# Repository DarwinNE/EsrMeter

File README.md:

# EsrMeter
An open hardware in-circuit ESR meter for electrolytic capacitors.

This circuit is based on a PIC16F883 that controls a simple lock-in circuit to measure in circuit the ESR and in some cases the capacitance of electrolytic capacitors.

The circuit has been designed by Davide Bucci, the PCB by Etenmenanki using Eagle. The size of the PCBs is compatible with the free version of the program.

A description (in italian language) of the circuit can be found here: https://www.electroyou.it/darwinne/wiki/misurare-esr-di-condensatori-con-circuito-lock-in

Two versions of the PCB exist. The first one has the digital and analog parts split in two. This approach has the advantage that one can test the analog board with something different from the PIC16F883 (i.e. a STM32 or an Arduino board, for instance). The version with the two boards separated requires some corrections, look at the associated files if you try to build them.
The second version has all digital and analog circuits on the same board and it is much more compact. I ordered the PCB on July 24, 2022, I received them and assembled a first prototype at the end of August 2022. It worked at the first attempt, but there is a shift in low ESR values and moderate to large capacitance (>300µF) that I am currently (mid Sept 2022) investigating.

All components are SMD. In the "all in one" boards, two different versions of the PIC16F883 can be used to cope with the pandemic scarcity of components: SOIC and SSOP. I think the PIC16F886 can be used at the place of the PIC16F883 with minimal changes.

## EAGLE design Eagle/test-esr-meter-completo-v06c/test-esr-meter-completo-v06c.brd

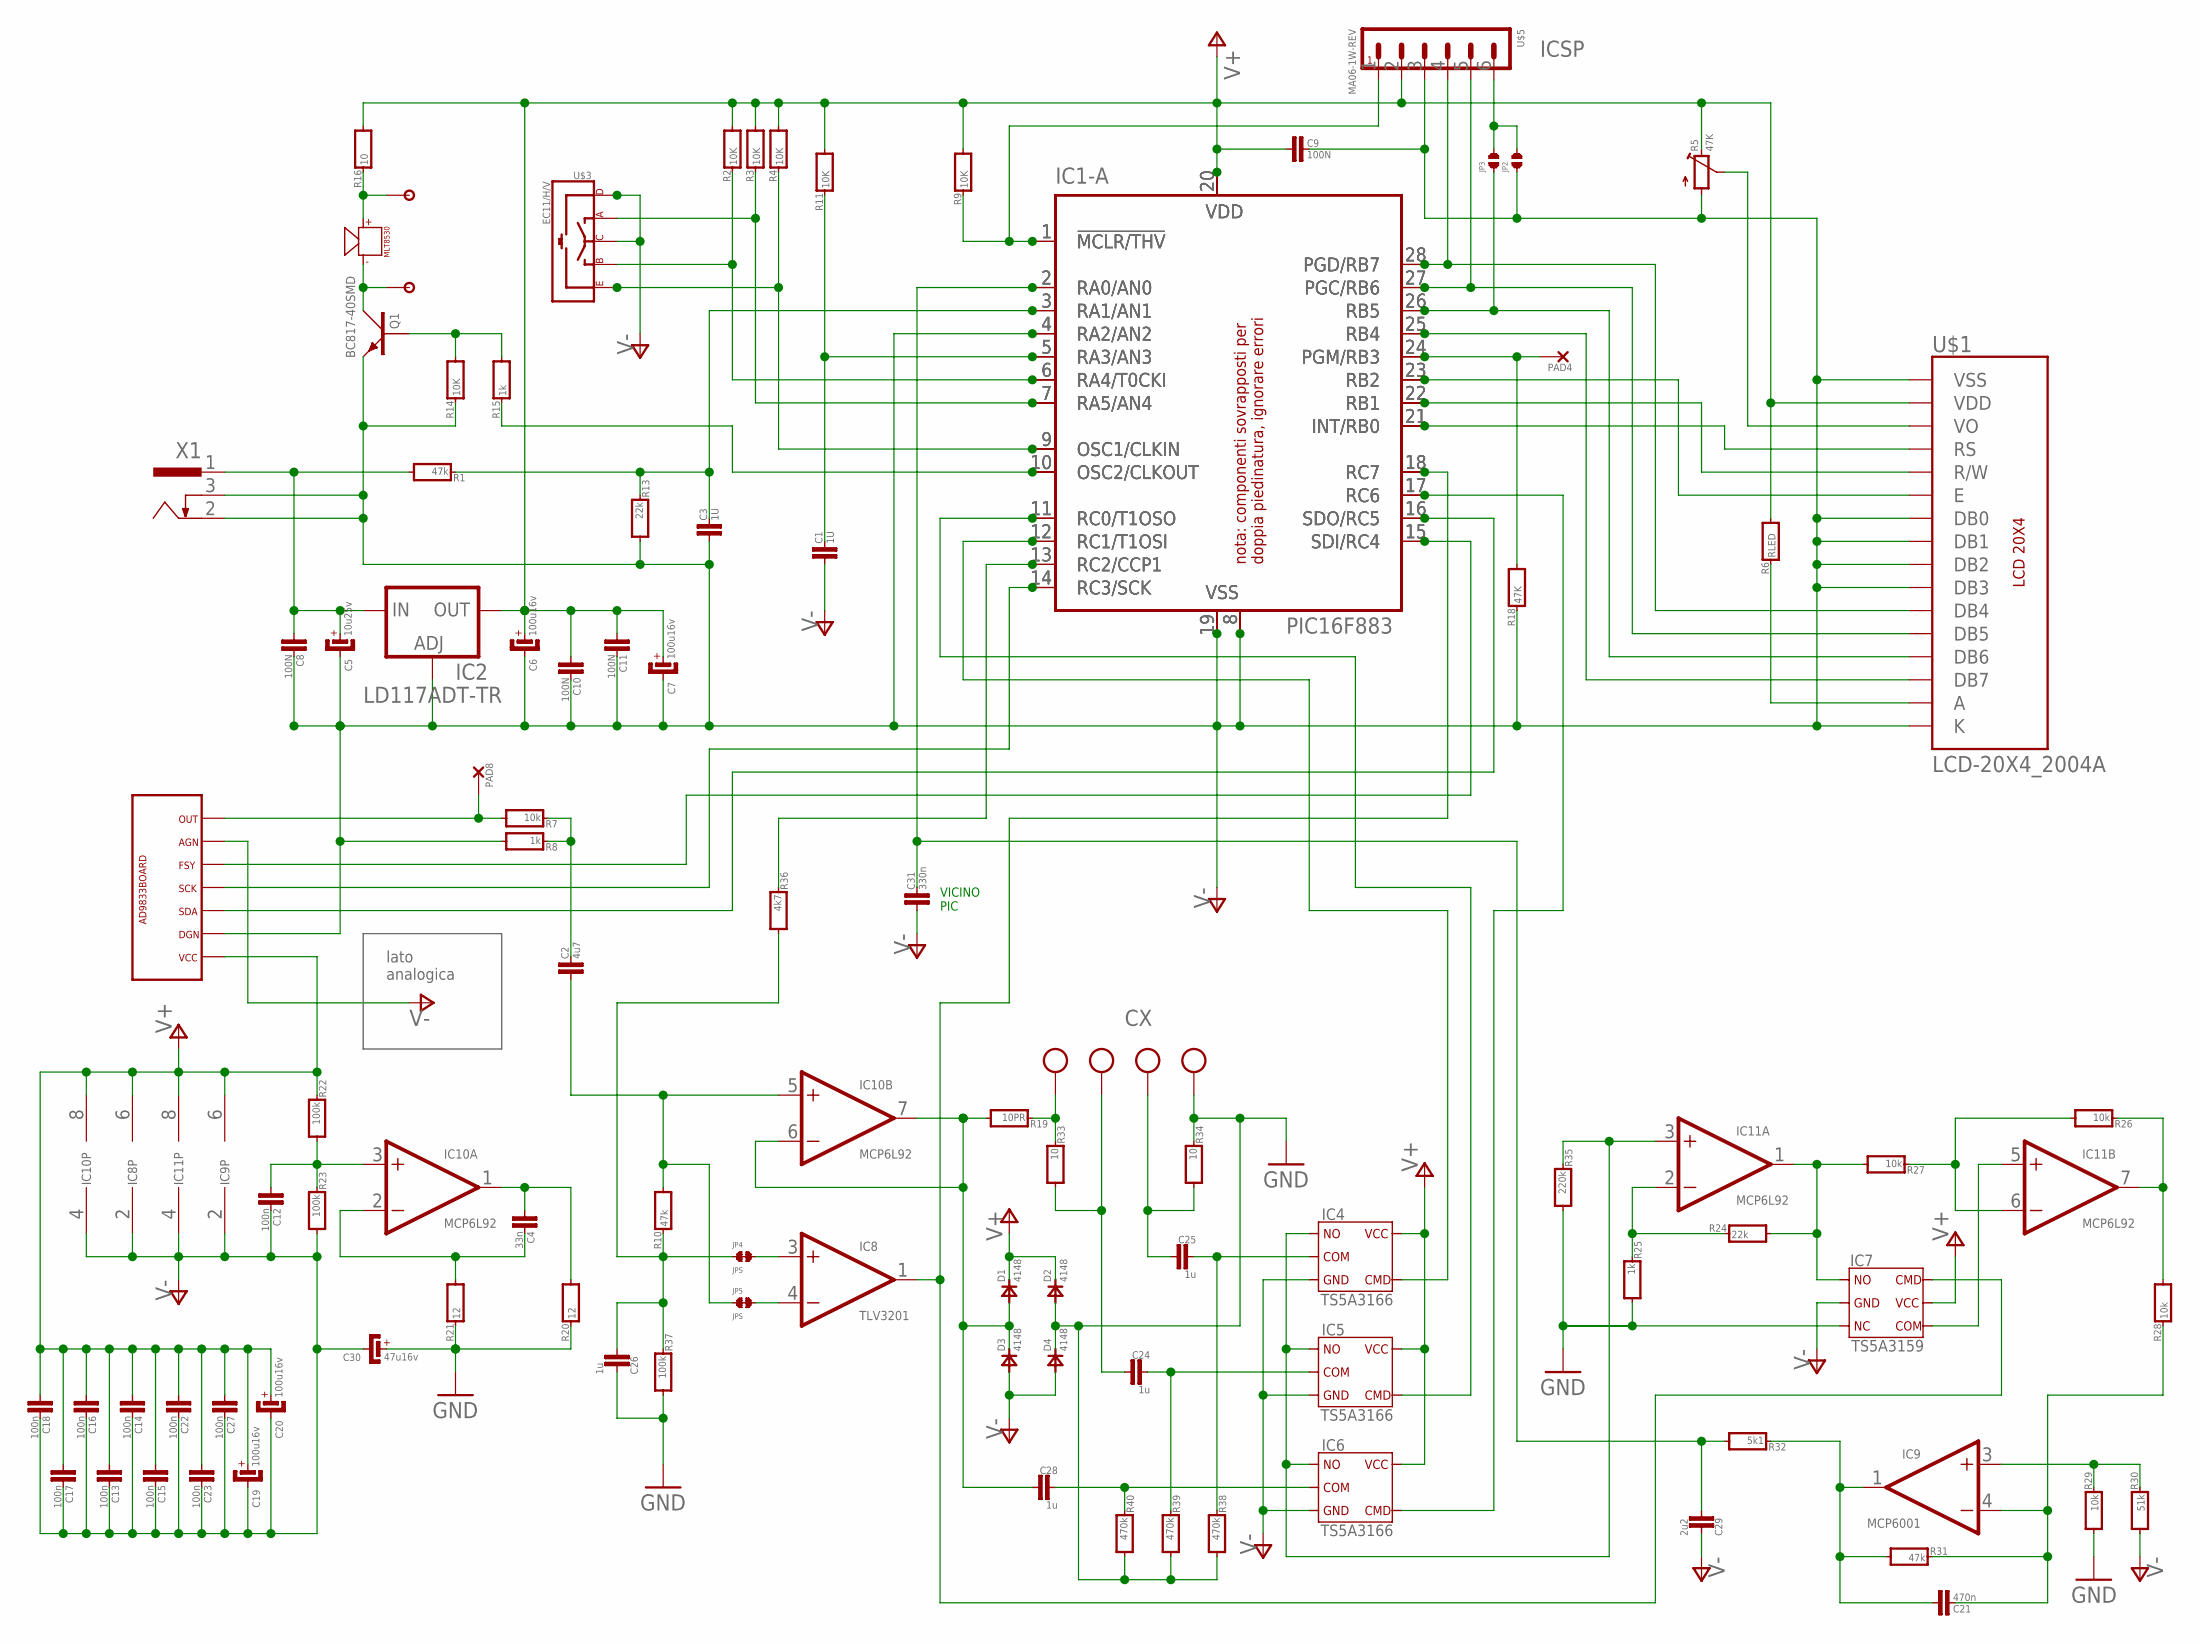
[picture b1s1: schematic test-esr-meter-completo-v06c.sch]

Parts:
C1, C3: 1U; C0805K
C2: 4u7; C0805K
C4: 33n; C0805K
C5: 10u25v; SMC_D
C6, C7, C19, C20: 100u16v; SMC_D
C8, C9, C10, C11: 100N; C0805K
C12, C13, C14, C15, C16, C17, C18, C22, C23, C27: 100n; C0805K
C21: 470n; C0805K
C24, C25, C26, C28: 1u; C0805K
C29: 2u2; C0805K
C30: 47u16v; SMC_B
C31: 330n; C0805K
D1, D2, D3, D4: 4148; SOD80C
IC1-A: PIC16F883; SO28W
IC2: LD117ADT-TR; DPACK
IC3: PIC16F872SS; SSOP28
IC4, IC5, IC6: TS5A3166; SOT23-5
IC7: TS5A3159; SOT23-6
IC8: TLV3201; SOT23-5
IC9: MCP6001; SOT23-5
IC10, IC11: MCP6L92; SO08
JP2, JP3: JPO
JP4, JP5: JPS
PAD4, PAD8: SMD2; SMD1,27-2,54
Q1: BC817-40SMD; SOT23-BEC
R1, R10, R31: 47k; R0805
R2, R3, R4, R9, R11, R14: 10K; R0805
R5: 47K; RTRIM3339P
R6: RLED; R0805
R7, R26, R27, R28, R29: 10k; R0805
R8, R15, R25: 1k; R0805
R13, R24: 22k; R0805
R16, R33, R34: 10; R0805
R18: 47K; R0805
R19: 10PR; R0805
R20, R21: 12; R0805
R22, R23, R37: 100k; R0805
R30: 51k; R0805
R32: 5k1; R0805
R35: 220k; R0805
R36: 4k7; R0805
R38, R39, R40: 470k; R0805
U$1: LCD-20X4_2004A
U$2: MLT-8530
U$3: EC11/H/V; EC11/V/H
U$4: AD9833BOARD
U$5: MA06-1W-REV
U$6, U$7: PIAZ08
X1: SCD-014A; SCD-014-A
X2: MKDSN1,5/4-5,08

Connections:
GND: C26.2, C30.+, D2.A, D4.C, IC7.3 (NC), R20.1, R21.1, R25.2, R29.2, R34.1, R35.2, R37.2, R38.2, R39.2, R40.2, X2.4
unnamed: IC1-A.10 (OSC2/CLKOUT), IC3.10 (OSC2/CLKOUT), R15.1
unnamed: C26.1, JP4.P$1, R10.1, R36.2, R37.1
unnamed: Q1.B, R14.2, R15.2
unnamed: IC1-A.28 (PGD/RB7), IC3.28 (PGD/RB7), U$1.11 (DB4), U$5.4
unnamed: IC1-A.14 (RC3/SCK), IC3.14 (RC3/SCK), U$4.SCK
unnamed: IC1-A.16 (SDO/RC5), IC3.16 (SDO/RC5), U$4.SDA
unnamed: IC1-A.15 (SDI/RC4), IC3.15 (SDI/RC4), U$4.FSY
unnamed: IC1-A.27 (PGC/RB6), IC3.27 (PGC/RB6), U$1.12 (DB5), U$5.5
unnamed: R5.2 (S), U$1.3 (VO)
unnamed: C2.2, IC10.5 (+IN), JP5.P$1, R10.2
unnamed: IC1-A.25 (RB4), IC3.25 (RB4), U$1.14 (DB7)
unnamed: C29.1, C31.1, IC1-A.2 (RA0/AN0), IC3.2 (RA0/AN0), R32.2
unnamed: C3.1, IC1-A.3 (RA1/AN1), IC3.3 (RA1/AN1), R1.1, R13.1
unnamed: C1.1, IC1-A.5 (RA3/AN3), IC3.5 (RA3/AN3), R11.1
unnamed: IC1-A.23 (RB2), IC3.23 (RB2), U$1.6 (E)
unnamed: IC1-A.22 (RB1), IC3.22 (RB1), U$1.5 (R/W)
unnamed: IC1-A.21 (INT/RB0), IC3.21 (INT/RB0), U$1.4 (RS)
unnamed: IC1-A.6 (RA4/T0CKI), IC3.6 (RA4/T0CKI), R2.1, U$3.B
unnamed: IC1-A.7 (RA5/AN4), IC3.7 (RA5/AN4), R3.1, U$3.A
unnamed: IC1-A.9 (OSC1/CLKIN), IC3.9 (OSC1/CLKIN), R4.1, U$3.E, U$3.E2
unnamed: IC1-A.17 (RC6), IC3.17 (RC6), IC6.4 (CMD)
unnamed: IC1-A.12 (RC1/T1OSI), IC3.12 (RC1/T1OSI), IC4.4 (CMD)
unnamed: IC1-A.11 (RC0/T1OSO), IC3.11 (RC0/T1OSO), IC5.4 (CMD)
unnamed: C24.1, R33.2, X2.2
unnamed: R6.1, U$1.15 (A)
unnamed: IC1-A.24 (PGM/RB3), IC3.24 (PGM/RB3), PAD4.1, R18.2
unnamed: IC1-A.18 (RC7), IC3.18 (RC7), IC7.6 (CMD), IC8.1 (OUT)
unnamed: IC4.1 (NO), IC5.1 (NO), IC6.1 (NO), IC11.3 (+IN), R35.1
unnamed: C5.+, C8.2, IC2.3 (IN), R1.2, X1.1
unnamed: C4.1, IC10.2 (-IN), R21.2
unnamed: R16.1, U$2.+, U$6.P$1
unnamed: IC1-A.1 (!MCLR/THV), IC3.1 (!MCLR/THV), R9.1, U$5.1
unnamed: IC1-A.26 (RB5), IC3.26 (RB5), JP3.P$1, U$1.13 (DB6)
unnamed: JP2.P$2, JP3.P$2, U$5.6
unnamed: Q1.C, U$2.-, U$7.P$1
unnamed: C4.2, IC10.1 (OUT), R20.2
unnamed: IC1-A.13 (RC2/CCP1), IC3.13 (RC2/CCP1), R36.1
unnamed: C12.2, IC10.3 (+IN), R22.2, R23.1
unnamed: IC11.2 (-IN), R24.1, R25.1
unnamed: IC7.1 (NO), IC11.1 (OUT), R24.2, R27.2
unnamed: IC11.7 (OUT), R26.1, R28.2
unnamed: IC11.6 (-IN), R26.2, R27.1
unnamed: IC7.4 (COM), IC11.5 (+IN)
unnamed: IC9.3 (+IN), R29.1, R30.1
unnamed: C21.1, IC9.4 (-IN), R28.1, R31.1
unnamed: C2.1, R7.1, R8.1
unnamed: PAD8.1, R7.2, U$4.OUT
unnamed: R19.1, R33.1, X2.1
unnamed: C25.1, R34.2, X2.3
unnamed: C28.1, D1.A, D3.C, IC10.6 (-IN), IC10.7 (OUT), R19.2
unnamed: C24.2, IC5.2 (COM), R39.1
unnamed: C25.2, IC4.2 (COM), R38.1
unnamed: C28.2, IC6.2 (COM), R40.1
unnamed: IC8.4 (-IN), JP5.P$2
unnamed: IC8.3 (+IN), JP4.P$2
unnamed: C21.2, IC9.1 (OUT), R31.2, R32.1
V+: C6.+, C7.+, C9.2, C10.2, C11.2, C13.2, C14.2, C15.2, C16.2, C17.2, C18.2, C19.+, C20.+, C22.2, C23.2, C27.2, D1.C, D2.C, IC1-A.20 (VDD), IC2.4 (OUT), IC3.20 (VDD), IC4.6 (V+), IC5.6 (V+), IC6.6 (V+), IC7.5 (V+), IC8.6 (V+), IC9.6 (V+), IC10.8 (V+), IC11.8 (V+), R2.2, R3.2, R4.2, R5.3 (E), R6.2, R9.2, R11.2, R16.2, R22.1, U$1.2 (VDD), U$4.VCC, U$5.2
V-: C1.2, C3.2, C5.-, C6.-, C7.-, C8.1, C9.1, C10.1, C11.1, C12.1, C13.1, C14.1, C15.1, C16.1, C17.1, C18.1, C19.-, C20.-, C22.1, C23.1, C27.1, C29.2, C30.-, C31.2, D3.A, D4.A, IC1-A.4 (RA2/AN2), IC1-A.8 (VSS), IC1-A.19 (VSS), IC2.1 (ADJ), IC3.4 (RA2/AN2), IC3.8 (VSS), IC3.19 (VSS), IC4.3 (GND), IC5.3 (GND), IC6.3 (GND), IC7.2 (GND), IC8.2 (V-), IC9.2 (V-), IC10.4 (V-), IC11.4 (V-), JP2.P$1, Q1.E, R5.1 (A), R8.2, R13.2, R14.1, R18.1, R23.2, R30.2, U$1.1 (VSS), U$1.7 (DB0), U$1.8 (DB1), U$1.9 (DB2), U$1.10 (DB3), U$1.16 (K), U$3.C, U$3.D, U$3.D2, U$4.AGN, U$4.DGN, U$5.3, X1.2, X1.3

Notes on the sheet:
ICSP
nota: componenti sovrapposti per doppia piedinatura, ignorare errori
VICINO PIC
lato analogica

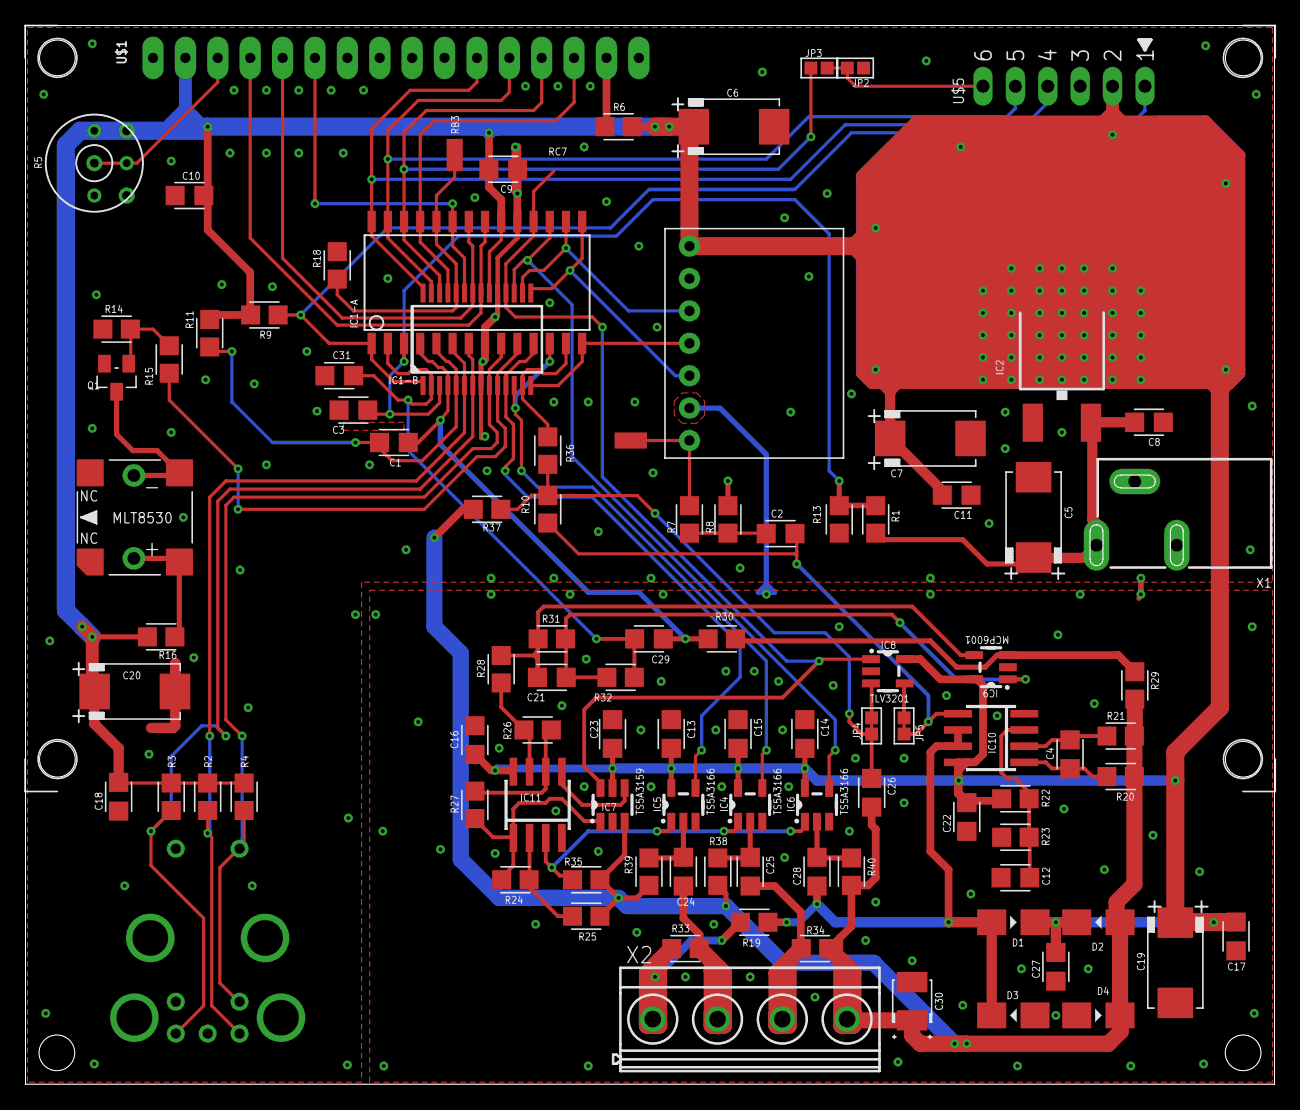
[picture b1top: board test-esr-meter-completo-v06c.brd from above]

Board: 2 copper layers, 97.9 x 83.0 mm, 100 parts (0 on the bottom side), 59 nets.

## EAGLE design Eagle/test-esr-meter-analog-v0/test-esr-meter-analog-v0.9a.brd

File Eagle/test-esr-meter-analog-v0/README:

CORREZIONI Parte analogica

- allungare tutte le piazzole delle resistenze e dei condensatori.
- portare C19 a 47µF invece di 10nF.
- portare C2 a 33nF invece di 10nF.
- portare C6, C7 e C20 a 1µF invece di 4,7µF?
- aggiungere tre resistenze da 470kΩ tra l'ingresso COM di IC4, IC5 e IC6 e GND (tengono a massa i condensatori C6, C7 e C20).
- portare C21 a 2,2µF invece che 1µF.
- portare C5 a 470nF invece che 330nF.
- portare R16 a 10kΩ invece che 47kΩ.
- portare R17 a 51kΩ invece che a 10kΩ.
- eliminare JP3.
- eliminare JP4 e collegare direttamente il piedino 1 di IC8 alla resistenza R19.

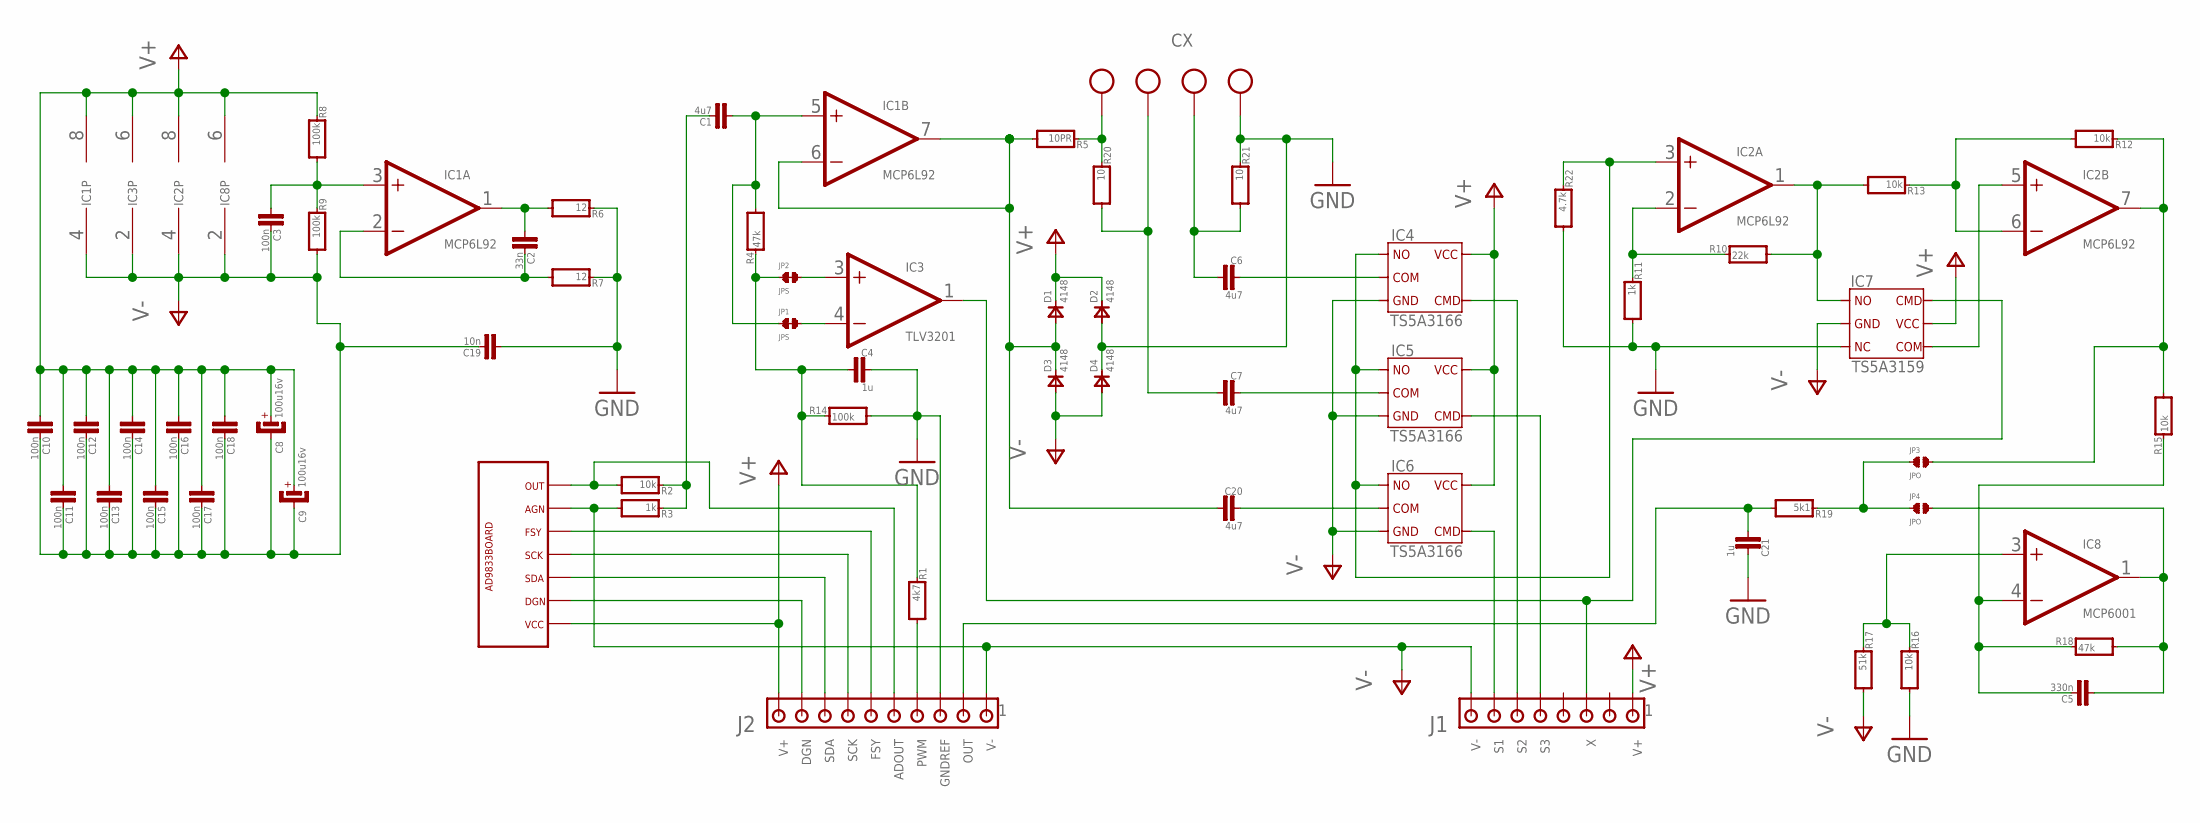
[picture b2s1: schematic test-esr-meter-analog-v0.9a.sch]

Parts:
C1, C6, C7, C20: 4u7; C0805K
C2: 33n; C0805K
C3, C10, C11, C12, C13, C14, C15, C16, C17, C18: 100n; C0805K
C4, C21: 1u; C0805K
C5: 330n; C0805K
C8, C9: 100u16v; SMC_D
C19: 10n; C0805K
D1, D2, D3, D4: 4148; SOD80C
IC1, IC2: MCP6L92; SO08
IC3: TLV3201; SOT23-5
IC4, IC5, IC6: TS5A3166; SOT23-5
IC7: TS5A3159; SOT23-6
IC8: MCP6001; SOT23-5
J1: MTA08-100; 10X08MTA
J2: MTA10-100; 10X10MTA
JP1, JP2: JPS
JP3, JP4: JPO
R1: 4k7; R0805
R2, R12, R13, R15, R16: 10k; R0805
R3, R11: 1k; R0805
R4, R18: 47k; R0805
R5: 10PR; R0805
R6, R7: 12; R0805
R8, R9, R14: 100k; R0805
R10: 22k; R0805
R17: 51k; R0805
R19: 5k1; R0805
R20, R21: 10; R0805
R22: 4.7k; R0805
U$1: AD9833BOARD
X2: MKDSN1,5/4-5,08

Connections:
GND: C4.2, C19.2, C21.2, D2.A, D4.C, IC7.3 (NC), J2.3, R6.1, R7.1, R11.2, R14.2, R16.2, R21.1, R22.2, X2.4
unnamed: C20.2, IC6.2 (COM)
unnamed: IC3.4 (-IN), JP1.P$2
unnamed: IC3.3 (+IN), JP2.P$2
unnamed: J2.4, R1.2
unnamed: C1.2, IC1.5 (+IN), JP1.P$1, R4.2
unnamed: C7.1, R20.2, X2.2
unnamed: IC2.3 (+IN), IC4.1 (NO), IC5.1 (NO), IC6.1 (NO), R22.1
unnamed: C2.1, IC1.2 (-IN), R7.2
unnamed: C2.2, IC1.1 (OUT), R6.2
unnamed: C3.2, IC1.3 (+IN), R8.2, R9.1
unnamed: IC2.2 (-IN), R10.1, R11.1
unnamed: IC2.1 (OUT), IC7.1 (NO), R10.2, R13.2
unnamed: IC6.4 (CMD), J1.7
unnamed: IC4.4 (CMD), J1.6
unnamed: IC5.4 (CMD), J1.5
unnamed: IC2.7 (OUT), JP3.P$2, R12.1, R15.2
unnamed: IC2.6 (-IN), R12.2, R13.1
unnamed: IC2.5 (+IN), IC7.4 (COM)
unnamed: IC3.1 (OUT), IC7.6 (CMD), J1.3
unnamed: IC8.3 (+IN), R16.1, R17.1
unnamed: C5.1, IC8.4 (-IN), R15.1, R18.1
unnamed: C5.2, IC8.1 (OUT), JP4.P$2, R18.2
unnamed: C21.1, J2.2, R19.2
unnamed: C1.1, R2.1, R3.1
unnamed: J2.5, R2.2, U$1.OUT
unnamed: J2.8, U$1.SDA
unnamed: J2.7, U$1.SCK
unnamed: J2.6, U$1.FSY
unnamed: R5.1, R20.1, X2.1
unnamed: C6.1, R21.2, X2.3
unnamed: J2.9, U$1.DGN
unnamed: C20.1, D1.A, D3.C, IC1.6 (-IN), IC1.7 (OUT), R5.2
unnamed: C7.2, IC5.2 (COM)
unnamed: C6.2, IC4.2 (COM)
unnamed: C4.1, JP2.P$1, R1.1, R4.1, R14.1
unnamed: JP3.P$1, JP4.P$1, R19.1
V+: C8.+, C9.+, C10.2, C11.2, C12.2, C13.2, C14.2, C15.2, C16.2, C17.2, C18.2, D1.C, D2.C, IC1.8 (V+), IC2.8 (V+), IC3.6 (V+), IC4.6 (V+), IC5.6 (V+), IC6.6 (V+), IC7.5 (V+), IC8.6 (V+), J1.1, J2.10, R8.1, U$1.VCC
V-: C3.1, C8.-, C9.-, C10.1, C11.1, C12.1, C13.1, C14.1, C15.1, C16.1, C17.1, C18.1, C19.1, D3.A, D4.A, IC1.4 (V-), IC2.4 (V-), IC3.2 (V-), IC4.3 (GND), IC5.3 (GND), IC6.3 (GND), IC7.2 (GND), IC8.2 (V-), J1.8, J2.1, R3.2, R9.2, R17.2, U$1.AGN

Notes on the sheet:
FSY
SDA
SCK
OUT
PWM
DGN
ADOUT
GNDREF

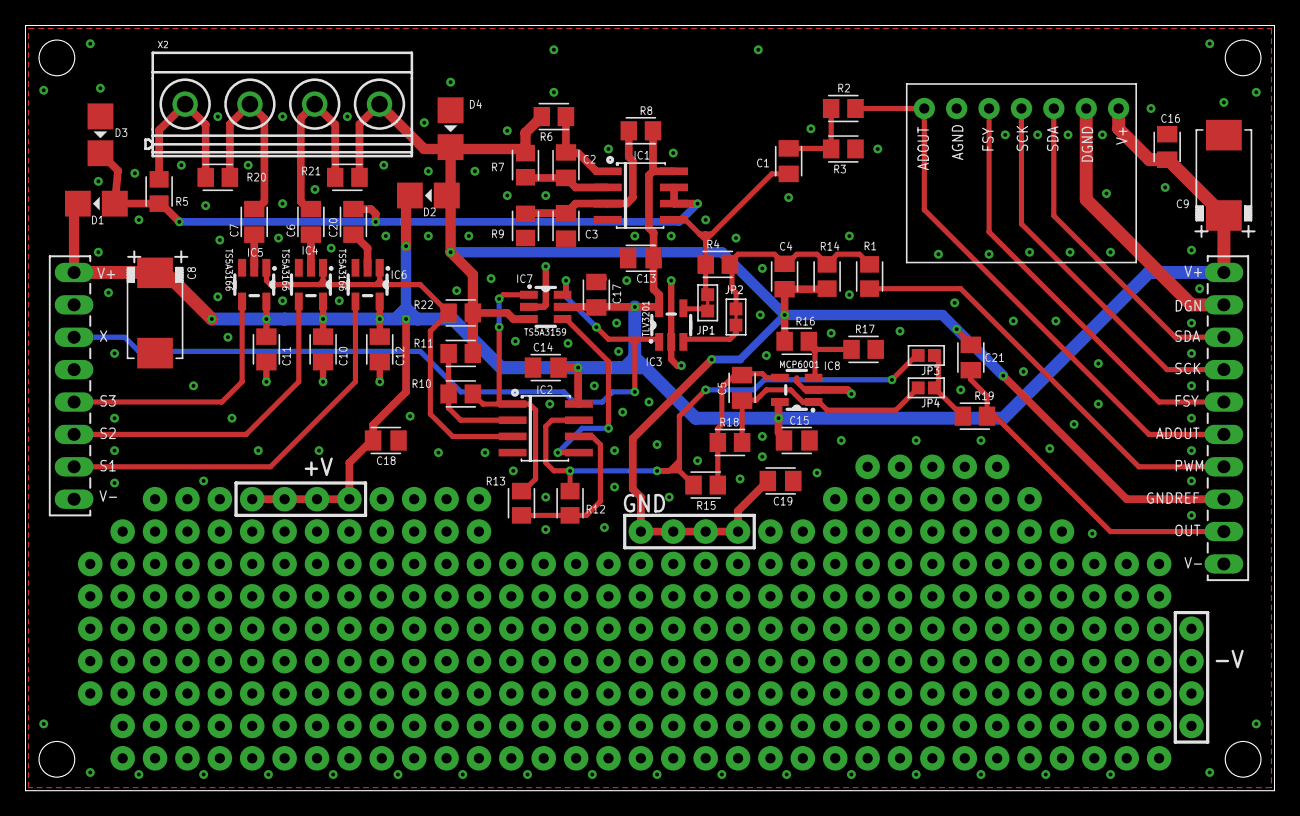
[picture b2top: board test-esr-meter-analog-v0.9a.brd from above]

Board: 2 copper layers, 97.9 x 60.0 mm, 63 parts (0 on the bottom side), 39 nets.

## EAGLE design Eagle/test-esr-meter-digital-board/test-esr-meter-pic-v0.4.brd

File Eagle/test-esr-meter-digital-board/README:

CORREZIONI Parte digitale

- invertire piedini 1,2 e 4,5 sul connettore ICSP. PGC va collegato sulla linea 5, PGD sulla linea 4; +V va sul piedino 2 e /MCLR/THV va sul piedino 1.
- invertire la numerazione 1 -> 6 a 6 -> 1, di modo che il piedino 1 si veda a destra guardando da sopra lo stampato. Ciò permette di inserire il PICkit2 in maniera più naturale con i led e la serigrafia verso l'alto.
- aggiungere un triangolo in serigrafia in corrispondenza del piedino 1 per facilitare l'inserimento corretto del PICkit2.
- invertire RC6 e RC2. In altre parole, RC6 deve andare a S1 mentre RC2 deve andare a PWM.
- portare R13 a 22kΩ al posto di 3,9kΩ.
- aggiungere un condensatore da 330 nF tra RA2 (GND) e RA0 (OUT), vicino al PIC.
- eliminare le resistenze R7, R8, R10, ho messo 0Ω e va benissimo.
- il regolatore di tensione IC2 dissipa soltanto 80 mW, probabilmente non c'è bisogno di una grande area ramata per dissipare il calore prodotto.
- ingrandire i fori per l'encoder. Perlomeno quello che usato ho io non ci entrava proprio.
- eliminare R12.
- collegare RC7 (pin 18) a X (uscita di IC3 sulla parte analogica)
- aggiungere una resistenza da 10kΩ tra PGM/RB3 e 0V (si veda pagina 224 del datasheet PIC16F883)

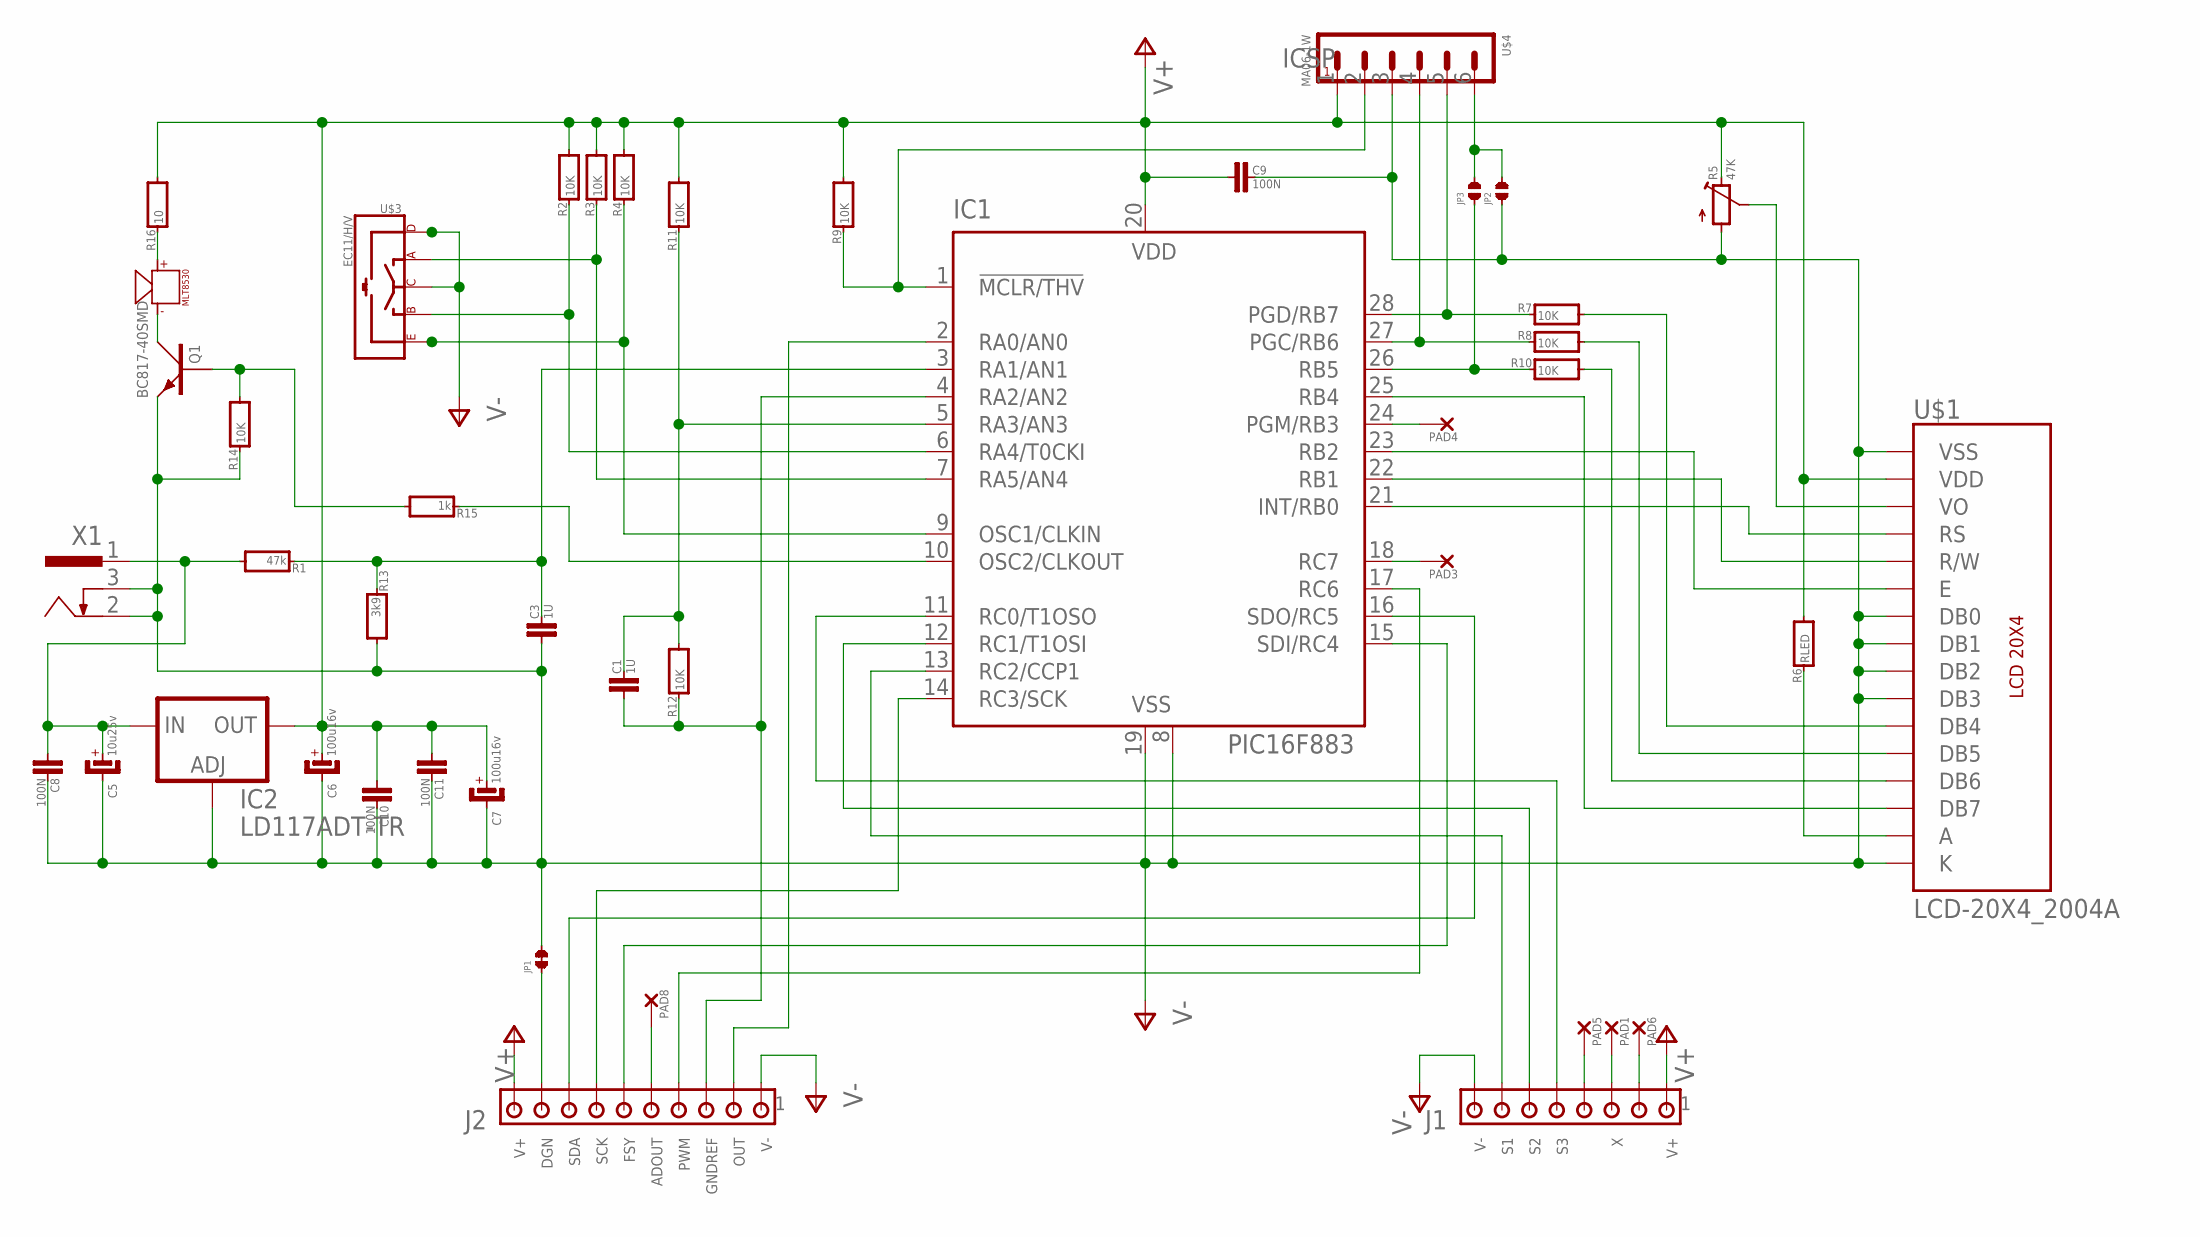
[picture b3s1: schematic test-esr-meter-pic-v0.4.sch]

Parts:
C1, C3: 1U; C0805K
C5: 10u25v; SMC_D
C6, C7: 100u16v; SMC_D
C8, C9, C10, C11: 100N; C0805K
IC1: PIC16F883; SO28W
IC2: LD117ADT-TR; DPACK
J1: MTA08-100; 10X08MTA
J2: MTA10-100; 10X10MTA
JP1: JPS
JP2, JP3: JPO
PAD1, PAD3, PAD4, PAD5, PAD6, PAD8: SMD2; SMD1,27-2,54
Q1: BC817-40SMD; SOT23-BEC
R1: 47k; R0805
R2, R3, R4, R7, R8, R9, R10, R11, R12, R14: 10K; R0805
R5: 47K; RTRIM3339P
R6: RLED; R0805
R13: 3k9; R0805
R15: 1k; R0805
R16: 10; R0805
U$1: LCD-20X4_2004A
U$2: MLT-8530
U$3: EC11/H/V; EC11/V/H
U$4: MA06-1W
X1: SCD-014A; SCD-014-A

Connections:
unnamed: IC1.10 (OSC2/CLKOUT), R15.1
unnamed: J2.9, JP1.P$1
unnamed: Q1.B, R14.2, R15.2
unnamed: R7.2, U$1.11 (DB4)
unnamed: IC1.14 (RC3/SCK), J2.7
unnamed: IC1.16 (SDO/RC5), J2.8
unnamed: IC1.15 (SDI/RC4), J2.6
unnamed: R8.2, U$1.12 (DB5)
unnamed: IC1.17 (RC6), J2.4
unnamed: R10.2, U$1.13 (DB6)
unnamed: IC1.25 (RB4), U$1.14 (DB7)
unnamed: IC1.2 (RA0/AN0), J2.2
unnamed: J2.5, PAD8.1
unnamed: C3.1, IC1.3 (RA1/AN1), R1.1, R13.1
unnamed: C1.1, IC1.5 (RA3/AN3), R11.1, R12.2
unnamed: J1.4, PAD5.1
unnamed: IC1.23 (RB2), U$1.6 (E)
unnamed: IC1.22 (RB1), U$1.5 (R/W)
unnamed: IC1.21 (INT/RB0), U$1.4 (RS)
unnamed: IC1.6 (RA4/T0CKI), R2.1, U$3.B
unnamed: IC1.7 (RA5/AN4), R3.1, U$3.A
unnamed: IC1.9 (OSC1/CLKIN), R4.1, U$3.E, U$3.E2
unnamed: IC1.13 (RC2/CCP1), J1.7
unnamed: IC1.12 (RC1/T1OSI), J1.6
unnamed: IC1.11 (RC0/T1OSO), J1.5
unnamed: J1.2, PAD6.1
unnamed: R5.2 (S), U$1.3 (VO)
unnamed: R6.1, U$1.15 (A)
unnamed: IC1.24 (PGM/RB3), PAD4.1
unnamed: IC1.18 (RC7), PAD3.1
unnamed: C1.2, IC1.4 (RA2/AN2), J2.3, R12.1
unnamed: IC1.27 (PGC/RB6), R8.1, U$4.4
unnamed: C5.+, C8.2, IC2.3 (IN), R1.2, X1.1
unnamed: IC1.28 (PGD/RB7), R7.1, U$4.5
unnamed: R16.1, U$2.+
unnamed: IC1.1 (!MCLR/THV), R9.1, U$4.2
unnamed: IC1.26 (RB5), JP3.P$1, R10.1
unnamed: JP2.P$2, JP3.P$2, U$4.6
unnamed: Q1.C, U$2.-
unnamed: J1.3, PAD1.1
V+: C6.+, C7.+, C9.2, C10.2, C11.2, IC1.20 (VDD), IC2.4 (OUT), J1.1, J2.10, R2.2, R3.2, R4.2, R5.3 (E), R6.2, R9.2, R11.2, R16.2, U$1.2 (VDD), U$4.1
V-: C3.2, C5.-, C6.-, C7.-, C8.1, C9.1, C10.1, C11.1, IC1.8 (VSS), IC1.19 (VSS), IC2.1 (ADJ), J1.8, J2.1, JP1.P$2, JP2.P$1, Q1.E, R5.1 (A), R13.2, R14.1, U$1.1 (VSS), U$1.7 (DB0), U$1.8 (DB1), U$1.9 (DB2), U$1.10 (DB3), U$1.16 (K), U$3.C, U$3.D, U$3.D2, U$4.3, X1.2, X1.3

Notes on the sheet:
FSY
SDA
SCK
OUT
PWM
DGN
ADOUT
ICSP
GNDREF

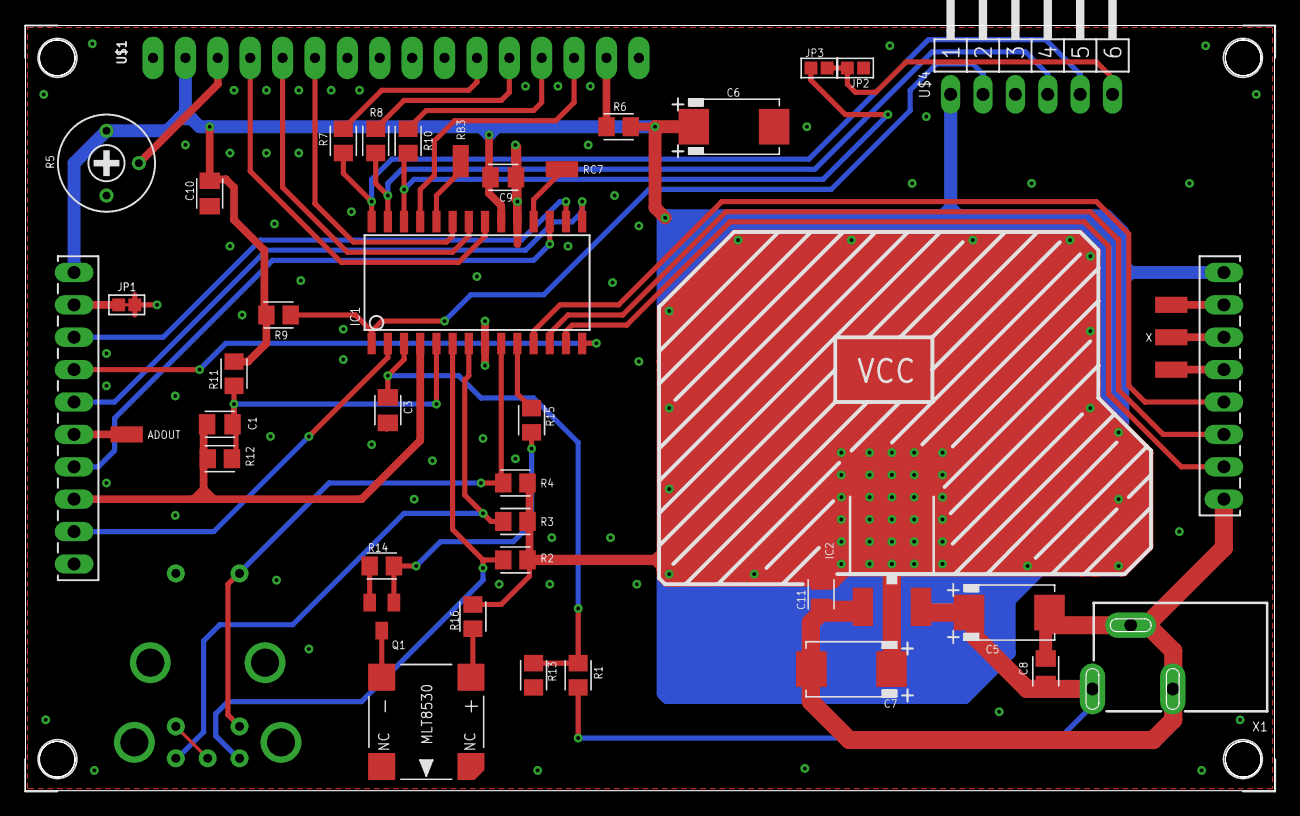
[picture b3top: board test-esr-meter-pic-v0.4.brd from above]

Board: 2 copper layers, 97.9 x 60.0 mm, 44 parts (0 on the bottom side), 42 nets.

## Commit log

2021-04-06 Initial import.
2021-04-06 Some slight modifications and comments to the source code.
2021-05-02 Added PCBs done with Eagle by Etemenanki of the Electroyou.it forum.
2021-06-02 Update some details and component values.
2021-06-27 Version with PIC16F883 on the PCB.
2021-06-27 Add DC bias mode.
2021-06-28 Tweaked details and improved some code.
2021-07-05 Check for low test current situations.
2021-07-12 Automatic measurement of capacitance and ESR. Still much to improve.
2021-07-13 Implement main menu.
2021-07-14 Tweaks here and there.
2021-07-18 Measure the battery voltage when switched on.
2021-07-23 Correct the number of ADC acquisitions.
2021-12-14 Removed the obsolete version for the prototype with the PIC16F690.
2021-12-19 Improved version, with better frequency ranging for the capacitance measurements. Still somewhat slow and some cluncky messages are shown on the display during the measurements.
2021-12-19 Cleaner messages when measuring the capacitance.
2021-12-19 Faster measurement of the capacitance.
2021-12-21 Improved measurements with longer time constants.
2021-12-21 Slight refactoring and improved comments on the code.
2021-12-21 Some refactoring and documentation.
2021-12-22 Better frequency selection algorithm to measure capacitance. Faster measurements.
2021-12-23 Better synchronization with oscillator during measurements.
2021-12-23 Add the control on ESR limits.
2022-01-24 Introducing calibration coefficients so to have precise measurements down to 10 nF.
2022-01-24 Added 2022 to the year...
2022-02-08 More reliable choice of when to measure ESR in automatic C mode.
2022-02-10 Tweaked a few coefficients, corrected bugs and implemented an algorithm to recognize resistances in automatic mode.
2022-03-09 Add minimum voltage test 6.7V for the battery.
2022-03-19 Emits a beep whose length is proportional to ESR.
2022-03-19 Refactored table code for DC value and frequency selection.
2022-03-19 Add a menu to activate/deactivate the beep.
2022-03-20 Corrected a bug that prevented beep length to be related to ESR.
2022-07-07 Improve speed to read large capacitors.
2022-07-07 Renamed directories containing the schematics and PCB's
2022-07-07 Added README files with corrections for the analog and digital boards.
2022-07-24 Add a single board version made by Etenmenanki of the ElectroYou forum.
2022-09-14 Add .hex and .lst file as requested in #1
2024-05-04 Add a 3D-printed box, designed with OpenSCAD.
2024-05-04 Merged changes.
